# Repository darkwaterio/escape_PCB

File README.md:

# ESCAPE ESC powered motor driver
Files for the escape board

#License

Designed by Dark Water Technologies. Distributed under a Creative Commons Attribution, Share-Alike license.
Development kits based on this product should be distributed under a similar license.
Commercial products using the Escape boards as a reference design need not comply with this license; further questions can be sent to team@darkwater.io.
Check license.txt for more information.

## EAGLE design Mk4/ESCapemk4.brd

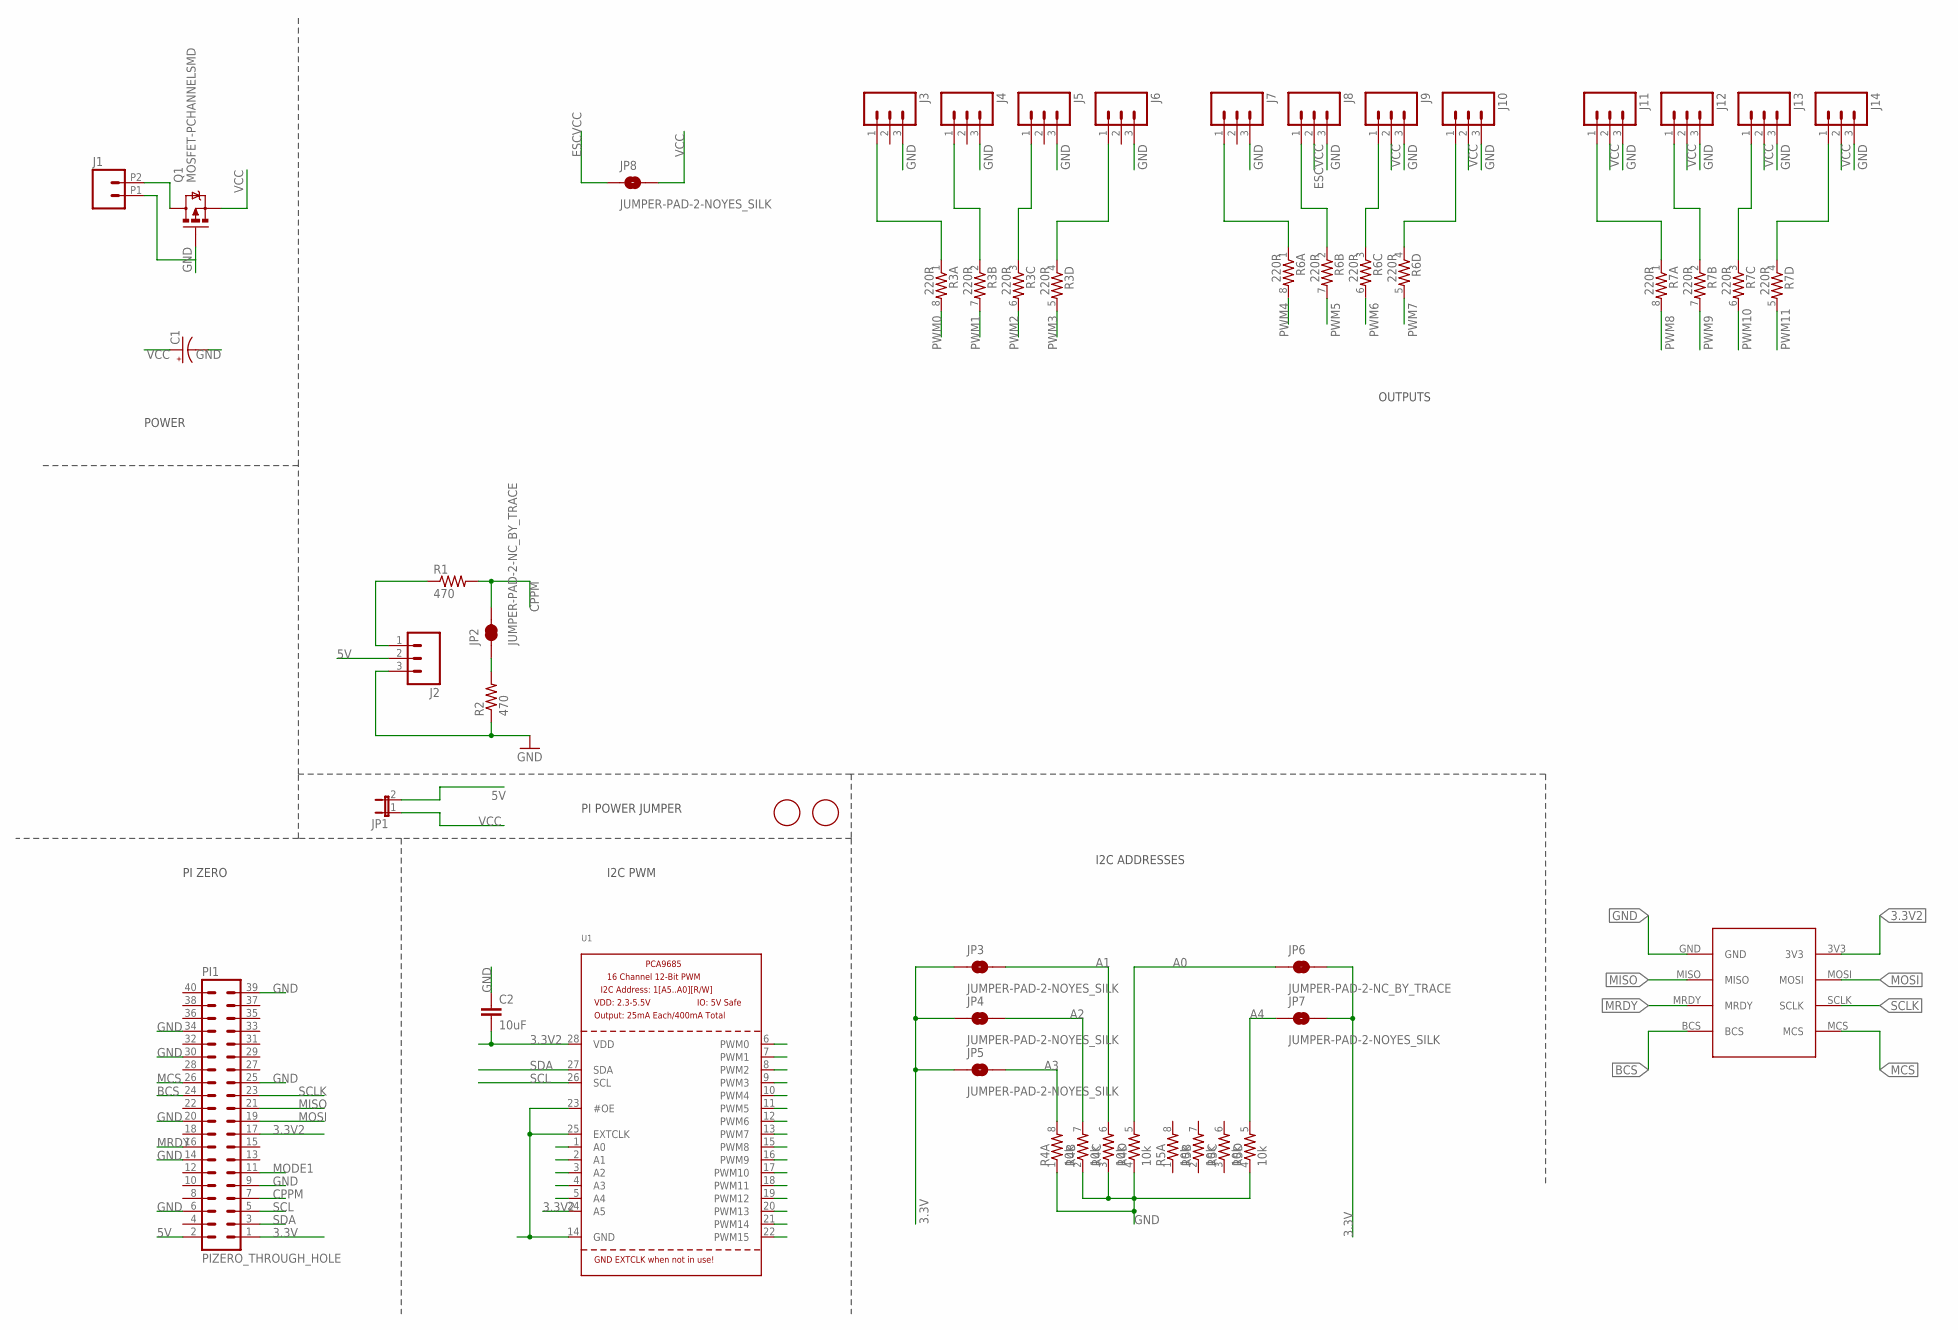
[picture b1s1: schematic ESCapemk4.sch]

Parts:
C1: CAP_POLPTH1; CPOL-RADIAL-100UF-25V
C2: 10uF; 0805
FID1, FID2: FIDUCIAL; FIDUCIAL_1MM
J1: M022.54MM_SCREWTERM; 1X02_2.54_SCREWTERM
J2, J3, J4, J5, J6, J7, J8, J9, J10, J11, J12, J13, J14: M03LOCK; 1X03_LOCK
JP1: JUMPER-2PTH_LOCK; 1X02_LOCK
JP2, JP6: JUMPER-PAD-2-NC_BY_TRACE; PAD-JUMPER-2-NC_BY_TRACE_YES_SILK
JP3, JP4, JP5, JP7, JP8: JUMPER-PAD-2-NOYES_SILK; PAD-JUMPER-2-NO_YES_SILK
PI1: PIZERO_THROUGH_HOLE; PIZERO_THOUGH_HOLE
Q1: MOSFET-PCHANNELSMD; SOT23-3
R1, R2: 470; 0805
R3, R6, R7: 220R; 0603-ARV
R4, R5: 10k; 0603-ARV
U1: PCA9685; TSSOP28
U$1: 2X4PADS

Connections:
3.3V: JP3.1, JP4.1, JP5.1, JP6.2, JP7.2, PI1.1
3.3V2: C2.2, PI1.17, U1.24 (A5), U1.28 (VDD), U$1.3V3
5V: J2.2, JP1.2, PI1.2
A0: JP6.1, R4.5 (2), U1.1 (A0)
A1: JP3.2, R4.6 (2), U1.2 (A1)
A2: JP4.2, R4.7 (2), U1.3 (A2)
A3: JP5.2, R4.8 (2), U1.4 (A3)
A4: JP7.1, R5.5 (2), U1.5 (A4)
BCS: PI1.24, U$1.BCS
CPPM: JP2.2, PI1.7, R1.2
ESCVCC: J8.2, JP8.1
GND: C1.2 (-), C2.1, J1.P1 (1), J2.3, J3.3, J4.3, J5.3, J6.3, J7.3, J8.3, J9.3, J10.3, J11.3, J12.3, J13.3, J14.3, PI1.6, PI1.9, PI1.14, PI1.20, PI1.25, PI1.30, PI1.34, PI1.39, Q1.1 (G), R2.1, R4.1, R4.2 (1), R4.3 (1), R4.4 (1), R5.4 (1), U1.14 (GND), U1.23 (#OE), U1.25 (EXTCLK), U$1.GND
MCS: PI1.26, U$1.MCS
MISO: PI1.21, U$1.MISO
MODE1: PI1.11
MOSI: PI1.19, U$1.MOSI
MRDY: PI1.16, U$1.MRDY
unnamed: J3.1, R3.1
unnamed: J4.1, R3.2 (1)
unnamed: J6.1, R3.4 (1)
unnamed: J5.1, R3.3 (1)
unnamed: J7.1, R6.1
unnamed: J8.1, R6.2 (1)
unnamed: J10.1, R6.4 (1)
unnamed: J9.1, R6.3 (1)
unnamed: J11.1, R7.1
unnamed: J12.1, R7.2 (1)
unnamed: J14.1, R7.4 (1)
unnamed: J13.1, R7.3 (1)
unnamed: J2.1, R1.1
unnamed: JP2.1, R2.2
unnamed: J1.P2 (2), Q1.3 (D)
PWM0: R3.8 (2), U1.6 (PWM0)
PWM1: R3.7 (2), U1.7 (PWM1)
PWM2: R3.6 (2), U1.8 (PWM2)
PWM3: R3.5 (2), U1.9 (PWM3)
PWM4: R6.8 (2), U1.10 (PWM4)
PWM5: R6.7 (2), U1.11 (PWM5)
PWM6: R6.6 (2), U1.12 (PWM6)
PWM7: R6.5 (2), U1.13 (PWM7)
PWM8: R7.8 (2), U1.15 (PWM8)
PWM9: R7.7 (2), U1.16 (PWM9)
PWM10: R7.6 (2), U1.17 (PWM10)
PWM11: R7.5 (2), U1.18 (PWM11)
PWM12: U1.19 (PWM12)
PWM13: U1.20 (PWM13)
PWM14: U1.21 (PWM14)
PWM15: U1.22 (PWM15)
SCL: PI1.5, U1.26 (SCL)
SCLK: PI1.23, U$1.SCLK
SDA: PI1.3, U1.27 (SDA)
VCC: C1.1 (+), J9.2, J10.2, J11.2, J12.2, J13.2, J14.2, JP1.1, JP8.2, Q1.2 (S)

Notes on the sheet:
I2C ADDRESSES
PI ZERO
I2C PWM
POWER
OUTPUTS
PI POWER JUMPER

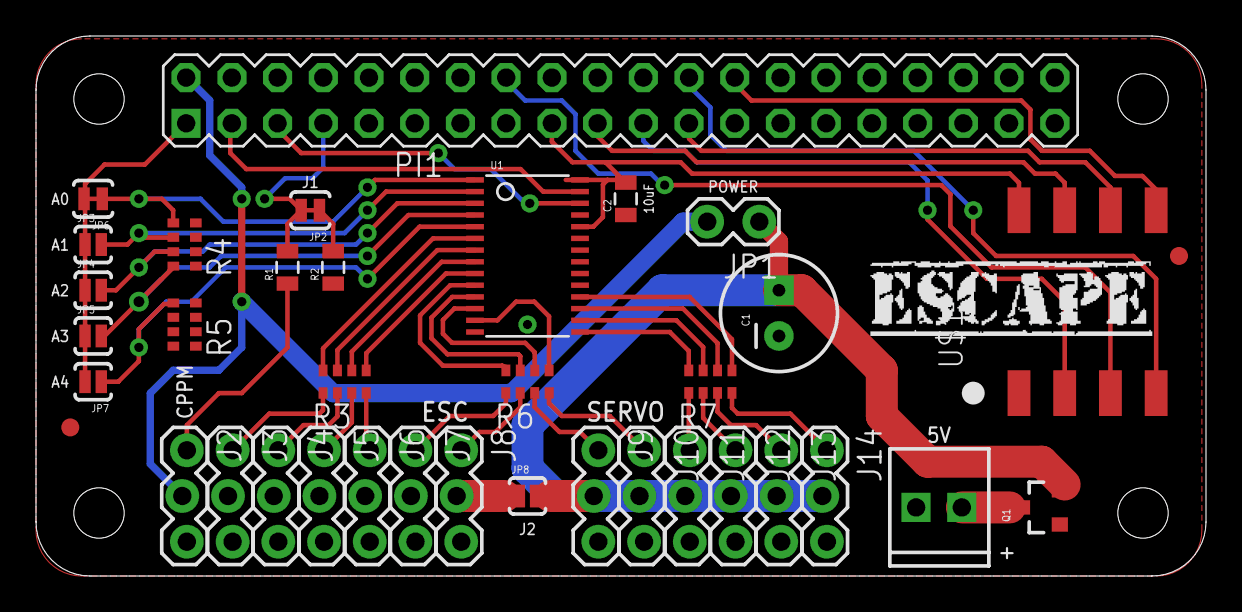
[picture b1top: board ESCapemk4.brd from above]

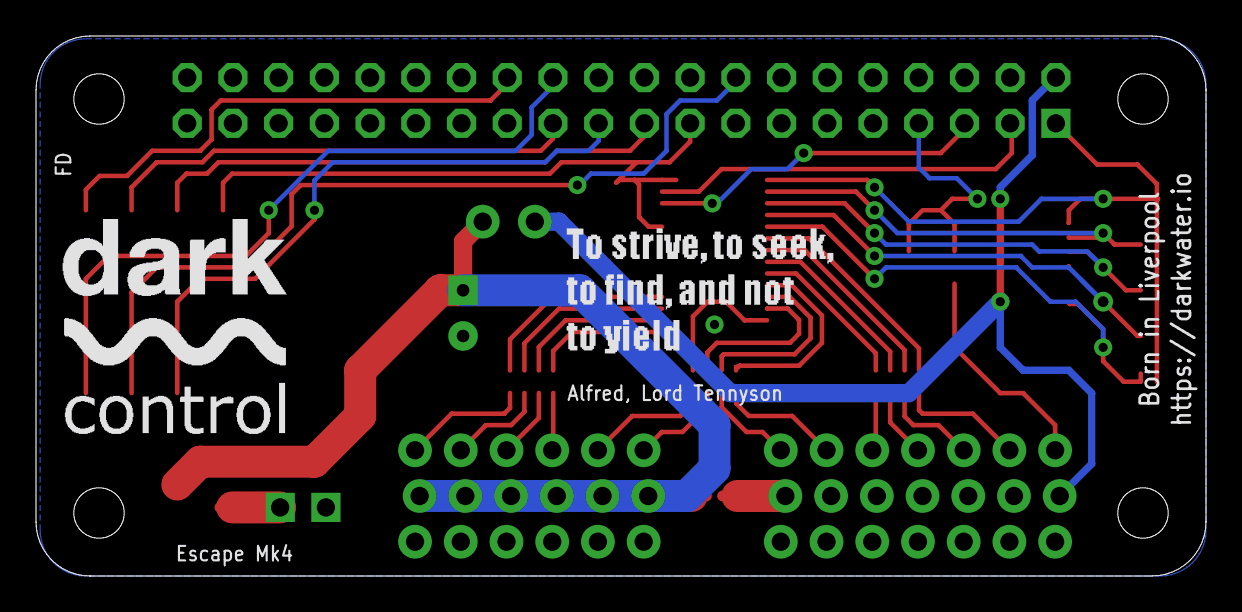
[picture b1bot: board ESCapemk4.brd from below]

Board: 2 copper layers, 65.0 x 30.0 mm, 40 parts (2 on the bottom side), 47 nets.

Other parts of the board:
U$2: DARKCONTROLSML
U$3: ESCAPEHORIZ
U$4: ULYSSES

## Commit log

2016-08-13 Moved from other repository
2016-08-13 license
2016-08-13 added license.txt
2016-11-12 Added Mk4 designs

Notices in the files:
parts and their libraries:
SparkFun-Connectors: Licensing: Creative Commons ShareAlike 4.0 International - https://creativecommons.org/licenses/by-sa/4.0
